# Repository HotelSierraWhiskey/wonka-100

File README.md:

# 🎩 The Wonka-100
## A barebones devboard to help make your dreams come true

The Wonka-100 features a SAMC21N18A TQFP microcontroller, TAG-Connet SWD + debug UART interface, and a JST GH series connector for power.

---

### Model

### Pinout

### SWD + Debug UART Interface

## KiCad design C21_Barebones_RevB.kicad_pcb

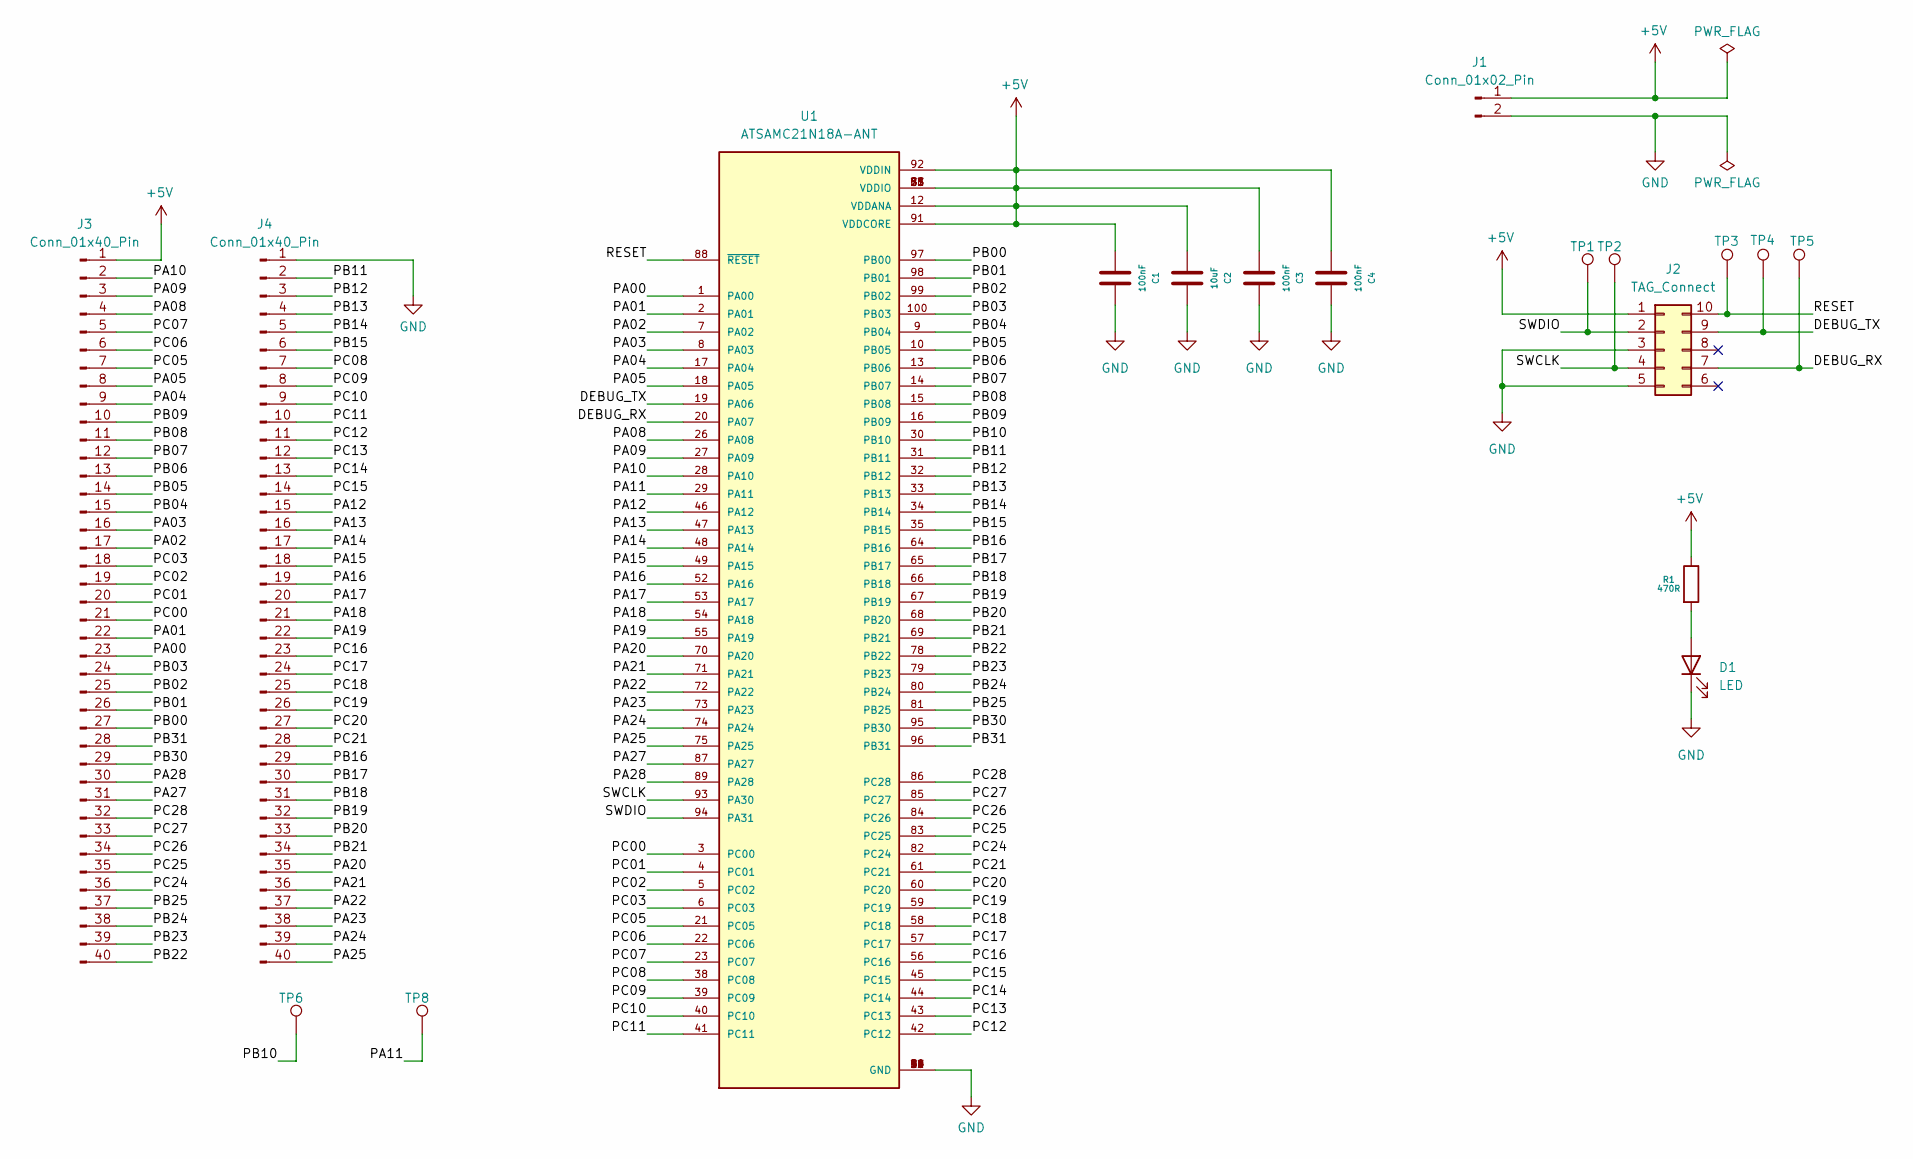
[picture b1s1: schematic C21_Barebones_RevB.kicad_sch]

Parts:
C1, C3, C4: 100nF; C_0603_1608Metric_Pad1.08x0.95mm_HandSolder; Manufacturer Part Number 0805B104K500NT; LCSC Part Number C49678
C2: 10uF; C_0603_1608Metric_Pad1.08x0.95mm_HandSolder; Manufacturer Part Number CL21A106KOQNNNE; LCSC Part Number C15850
D1: LED; LED_0603_1608Metric
J1: Conn_01x02_Pin; JST_GH_SM02B-GHS-TB_1x02-1MP_P1.25mm_Horizontal
J2: TAG_Connect; Tag-Connect_TC2050-IDC-FP_2x05_P1.27mm_Vertical
J3, J4: Conn_01x40_Pin; PinHeader_1x40_P2.54mm_Vertical
R1: 470R; R_0603_1608Metric_Pad0.98x0.95mm_HandSolder; LCSC Part Number C2094725
TP1, TP2, TP3, TP4, TP5, TP6, TP8: TestPoint; TestPoint_THTPad_D1.0mm_Drill0.5mm
U1: ATSAMC21N18A-ANT; QFP50P1600X1600X120-100N; PARTREV F; DigiKey_Part_Number ATSAMC21N18A-ANTTR-ND

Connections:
+5V: C1.1, C2.1, C3.1, C4.1, J1.1, J2.1, J3.1, R1.1, U1.12 (VDDANA), U1.25 (VDDIO), U1.36 (VDDIO), U1.51 (VDDIO), U1.63 (VDDIO), U1.77 (VDDIO), U1.91 (VDDCORE), U1.92 (VDDIN)
/DEBUG_RX: J2.7, TP5.1, U1.20 (PA07)
/DEBUG_TX: J2.9, TP4.1, U1.19 (PA06)
/PA00: J3.23, U1.1 (PA00)
/PA01: J3.22, U1.2 (PA01)
/PA02: J3.17, U1.7 (PA02)
/PA03: J3.16, U1.8 (PA03)
/PA04: J3.9, U1.17 (PA04)
/PA05: J3.8, U1.18 (PA05)
/PA08: J3.4, U1.26 (PA08)
/PA09: J3.3, U1.27 (PA09)
/PA10: J3.2, U1.28 (PA10)
/PA11: TP8.1, U1.29 (PA11)
/PA12: J4.15, U1.46 (PA12)
/PA13: J4.16, U1.47 (PA13)
/PA14: J4.17, U1.48 (PA14)
/PA15: J4.18, U1.49 (PA15)
/PA16: J4.19, U1.52 (PA16)
/PA17: J4.20, U1.53 (PA17)
/PA18: J4.21, U1.54 (PA18)
/PA19: J4.22, U1.55 (PA19)
/PA20: J4.35, U1.70 (PA20)
/PA21: J4.36, U1.71 (PA21)
/PA22: J4.37, U1.72 (PA22)
/PA23: J4.38, U1.73 (PA23)
/PA24: J4.39, U1.74 (PA24)
/PA25: J4.40, U1.75 (PA25)
/PA27: J3.31, U1.87 (PA27)
/PA28: J3.30, U1.89 (PA28)
/PB00: J3.27, U1.97 (PB00)
/PB01: J3.26, U1.98 (PB01)
/PB02: J3.25, U1.99 (PB02)
/PB03: J3.24, U1.100 (PB03)
/PB04: J3.15, U1.9 (PB04)
/PB05: J3.14, U1.10 (PB05)
/PB06: J3.13, U1.13 (PB06)
/PB07: J3.12, U1.14 (PB07)
/PB08: J3.11, U1.15 (PB08)
/PB09: J3.10, U1.16 (PB09)
/PB10: TP6.1, U1.30 (PB10)
/PB11: J4.2, U1.31 (PB11)
/PB12: J4.3, U1.32 (PB12)
/PB13: J4.4, U1.33 (PB13)
/PB14: J4.5, U1.34 (PB14)
/PB15: J4.6, U1.35 (PB15)
/PB16: J4.29, U1.64 (PB16)
/PB17: J4.30, U1.65 (PB17)
/PB18: J4.31, U1.66 (PB18)
/PB19: J4.32, U1.67 (PB19)
/PB20: J4.33, U1.68 (PB20)
/PB21: J4.34, U1.69 (PB21)
/PB22: J3.40, U1.78 (PB22)
/PB23: J3.39, U1.79 (PB23)
/PB24: J3.38, U1.80 (PB24)
/PB25: J3.37, U1.81 (PB25)
/PB30: J3.29, U1.95 (PB30)
/PB31: J3.28, U1.96 (PB31)
/PC00: J3.21, U1.3 (PC00)
/PC01: J3.20, U1.4 (PC01)
/PC02: J3.19, U1.5 (PC02)
/PC03: J3.18, U1.6 (PC03)
/PC05: J3.7, U1.21 (PC05)
/PC06: J3.6, U1.22 (PC06)
/PC07: J3.5, U1.23 (PC07)
/PC08: J4.7, U1.38 (PC08)
/PC09: J4.8, U1.39 (PC09)
/PC10: J4.9, U1.40 (PC10)
/PC11: J4.10, U1.41 (PC11)
/PC12: J4.11, U1.42 (PC12)
/PC13: J4.12, U1.43 (PC13)
/PC14: J4.13, U1.44 (PC14)
/PC15: J4.14, U1.45 (PC15)
/PC16: J4.23, U1.56 (PC16)
/PC17: J4.24, U1.57 (PC17)
/PC18: J4.25, U1.58 (PC18)
/PC19: J4.26, U1.59 (PC19)
/PC20: J4.27, U1.60 (PC20)
/PC21: J4.28, U1.61 (PC21)
/PC24: J3.36, U1.82 (PC24)
/PC25: J3.35, U1.83 (PC25)
/PC26: J3.34, U1.84 (PC26)
/PC27: J3.33, U1.85 (PC27)
/PC28: J3.32, U1.86 (PC28)
/RESET: J2.10, TP3.1, U1.88 (~RESET)
/SWCLK: J2.4, TP2.1, U1.93 (PA30)
/SWDIO: J2.2, TP1.1, U1.94 (PA31)
GND: C1.2, C2.2, C3.2, C4.2, D1.1 (K), J1.2, J2.3, J2.5, J4.1, U1.11 (GND), U1.24 (GND), U1.37 (GND), U1.50 (GND), U1.62 (GND), U1.76 (GND), U1.90 (GND)
unnamed: D1.2 (A), R1.2

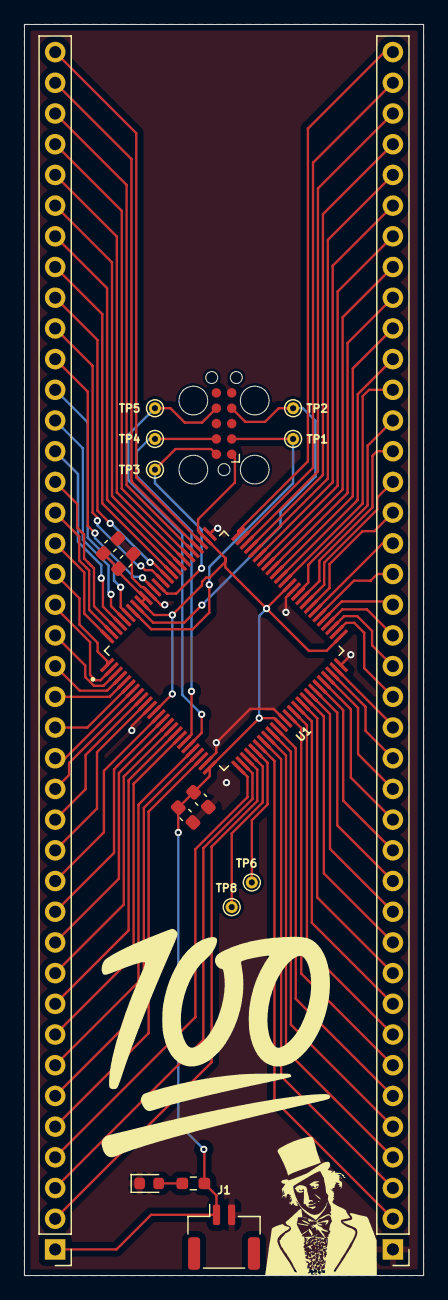
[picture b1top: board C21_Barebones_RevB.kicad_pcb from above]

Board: 2 copper layers, 33.0 x 103.5 mm, 18 parts (0 on the bottom side), 88 nets.

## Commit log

2025-03-16 Added readme
